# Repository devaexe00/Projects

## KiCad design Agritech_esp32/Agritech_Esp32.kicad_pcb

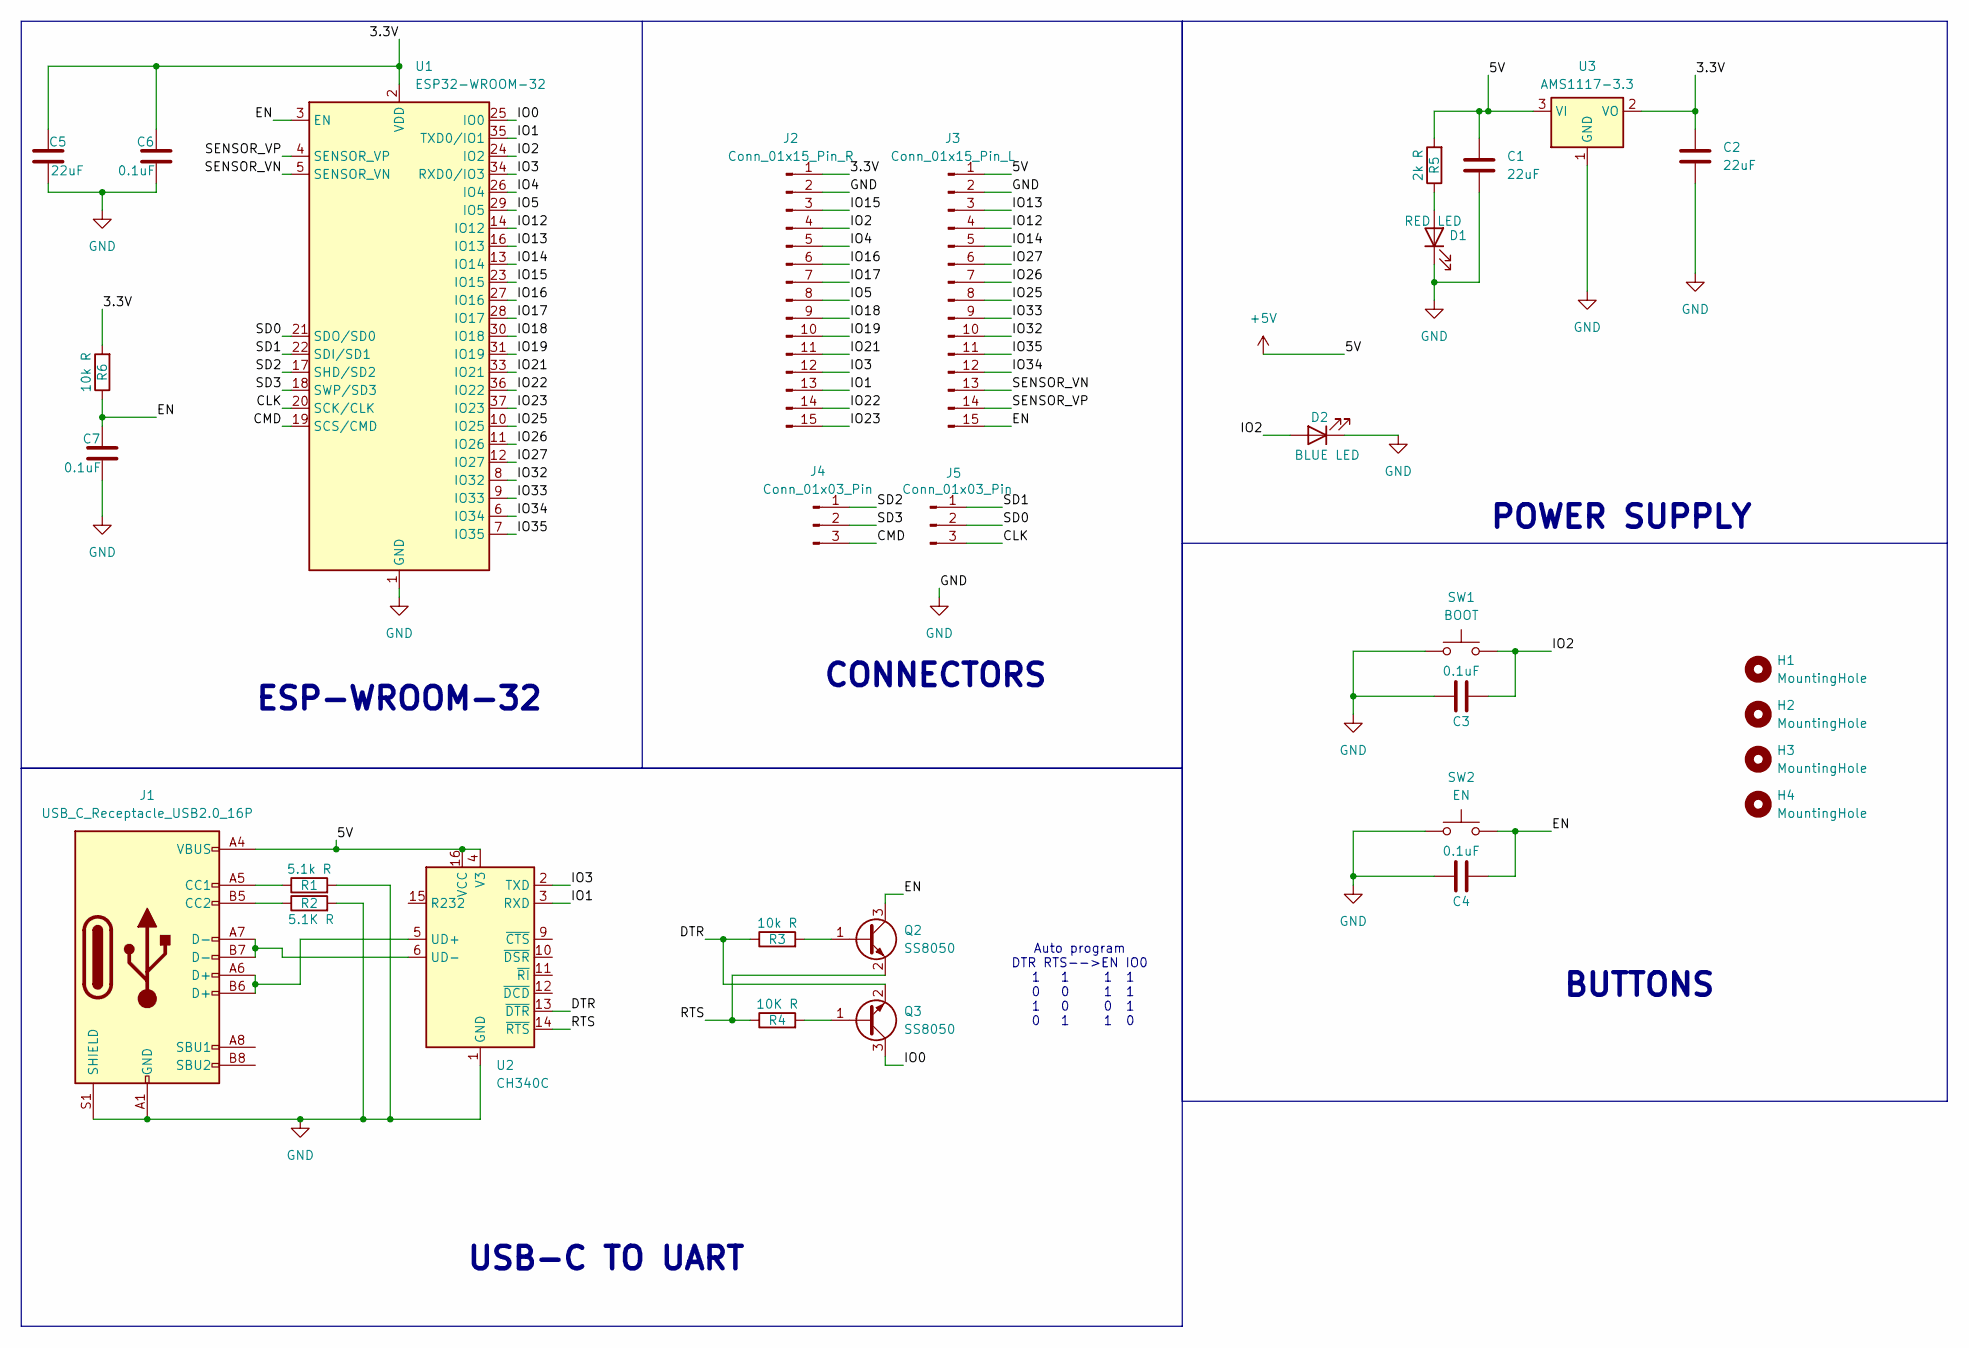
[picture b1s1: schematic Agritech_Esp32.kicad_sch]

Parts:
C1, C2, C5: 22uF; CP_Radial_D5.0mm_P2.50mm
C3, C4, C6, C7: 0.1uF; CP_Radial_D5.0mm_P2.50mm
D1: RED LED; LED_D5.0mm
D2: BLUE LED; LED_D5.0mm
H1, H2, H3, H4: MountingHole; MountingHole_2.5mm
J1: USB_C_Receptacle_USB2.0_16P; USB_C_Receptacle_HRO_TYPE-C-31-M-12
J2: Conn_01x15_Pin_R; PinHeader_1x15_P2.54mm_Vertical
J3: Conn_01x15_Pin_L; PinHeader_1x15_P2.54mm_Vertical
J4, J5: Conn_01x03_Pin; PinHeader_1x03_P2.54mm_Vertical
Q2, Q3: SS8050; SOT-23
R1: 5.1k R; R_Axial_DIN0309_L9.0mm_D3.2mm_P12.70mm_Horizontal
R2: 5.1K R; R_Axial_DIN0309_L9.0mm_D3.2mm_P12.70mm_Horizontal
R3, R6: 10k R; R_Axial_DIN0309_L9.0mm_D3.2mm_P12.70mm_Horizontal
R4: 10K R; R_Axial_DIN0309_L9.0mm_D3.2mm_P12.70mm_Horizontal
R5: 2k R; R_Axial_DIN0309_L9.0mm_D3.2mm_P12.70mm_Horizontal
SW1: BOOT; SW_Push_1P1T_NO_CK_KSC7xxJ
SW2: EN; SW_Push_1P1T_NO_CK_KSC7xxJ
U1: ESP32-WROOM-32
U2: CH340C; SOIC-16_3.9x9.9mm_P1.27mm
U3: AMS1117-3.3; SOT-223-3_TabPin2

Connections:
+5V: C1.1, J1.A4 (VBUS), J1.A9 (VBUS), J1.B4 (VBUS), J1.B9 (VBUS), J3.1, R5.2, U2.4 (V3), U2.16 (VCC), U3.3 (VI)
/3.3V: C2.1, C5.1, C6.2, J2.1, R6.2, U1.2 (VDD), U3.2 (VO)
/CLK: J5.3, U1.20 (SCK/CLK)
/CMD: J4.3, U1.19 (SCS/CMD)
/DTR: Q3.2 (E), R3.1, U2.13 (~DTR)
/EN: C4.2, C7.2, J3.15, Q2.3 (C), R6.1, SW2.2, U1.3 (EN)
/IO0: Q3.3 (C), U1.25 (IO0)
/IO1: J2.13, U1.35 (TXD0/IO1), U2.3 (RXD)
/IO2: C3.2, D2.2 (A), J2.4, SW1.2, U1.24 (IO2)
/IO3: J2.12, U1.34 (RXD0/IO3), U2.2 (TXD)
/IO4: J2.5, U1.26 (IO4)
/IO5: J2.8, U1.29 (IO5)
/IO12: J3.4, U1.14 (IO12)
/IO13: J3.3, U1.16 (IO13)
/IO14: J3.5, U1.13 (IO14)
/IO15: J2.3, U1.23 (IO15)
/IO16: J2.6, U1.27 (IO16)
/IO17: J2.7, U1.28 (IO17)
/IO18: J2.9, U1.30 (IO18)
/IO19: J2.10, U1.31 (IO19)
/IO21: J2.11, U1.33 (IO21)
/IO22: J2.14, U1.36 (IO22)
/IO23: J2.15, U1.37 (IO23)
/IO25: J3.8, U1.10 (IO25)
/IO26: J3.7, U1.11 (IO26)
/IO27: J3.6, U1.12 (IO27)
/IO32: J3.10, U1.8 (IO32)
/IO33: J3.9, U1.9 (IO33)
/IO34: J3.12, U1.6 (IO34)
/IO35: J3.11, U1.7 (IO35)
/RTS: Q2.2 (E), R4.1, U2.14 (~RTS)
/SD0: J5.2, U1.21 (SDO/SD0)
/SD1: J5.1, U1.22 (SDI/SD1)
/SD2: J4.1, U1.17 (SHD/SD2)
/SD3: J4.2, U1.18 (SWP/SD3)
/SENSOR_VN: J3.13, U1.5 (SENSOR_VN)
/SENSOR_VP: J3.14, U1.4 (SENSOR_VP)
GND: C1.2, C2.2, C3.1, C4.1, C5.2, C6.1, C7.1, D1.1 (K), D2.1 (K), J1.A1 (GND), J1.A12 (GND), J1.B1 (GND), J1.B12 (GND), J1.S1 (SHIELD), J2.2, J3.2, R1.2, R2.2, SW1.1, SW2.1, U1.1 (GND), U1.15 (GND), U1.38 (GND), U1.39 (GND), U2.1 (GND), U3.1 (GND)
unnamed: D1.2 (A), R5.1
unnamed: J1.A5 (CC1), R1.1
unnamed: J1.B5 (CC2), R2.1
unnamed: Q2.1 (B), R3.2
unnamed: Q3.1 (B), R4.2
unnamed: J1.A6 (D+), J1.B6 (D+), U2.5 (UD+)
unnamed: J1.A7 (D-), J1.B7 (D-), U2.6 (UD-)

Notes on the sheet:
USB-C TO UART
ESP-WROOM-32
POWER SUPPLY
Auto program DTR RTS-->EN IO0 1 1 1 1 0 0 1 1 1 0 0 1 0 1 1 0
CONNECTORS
BUTTONS

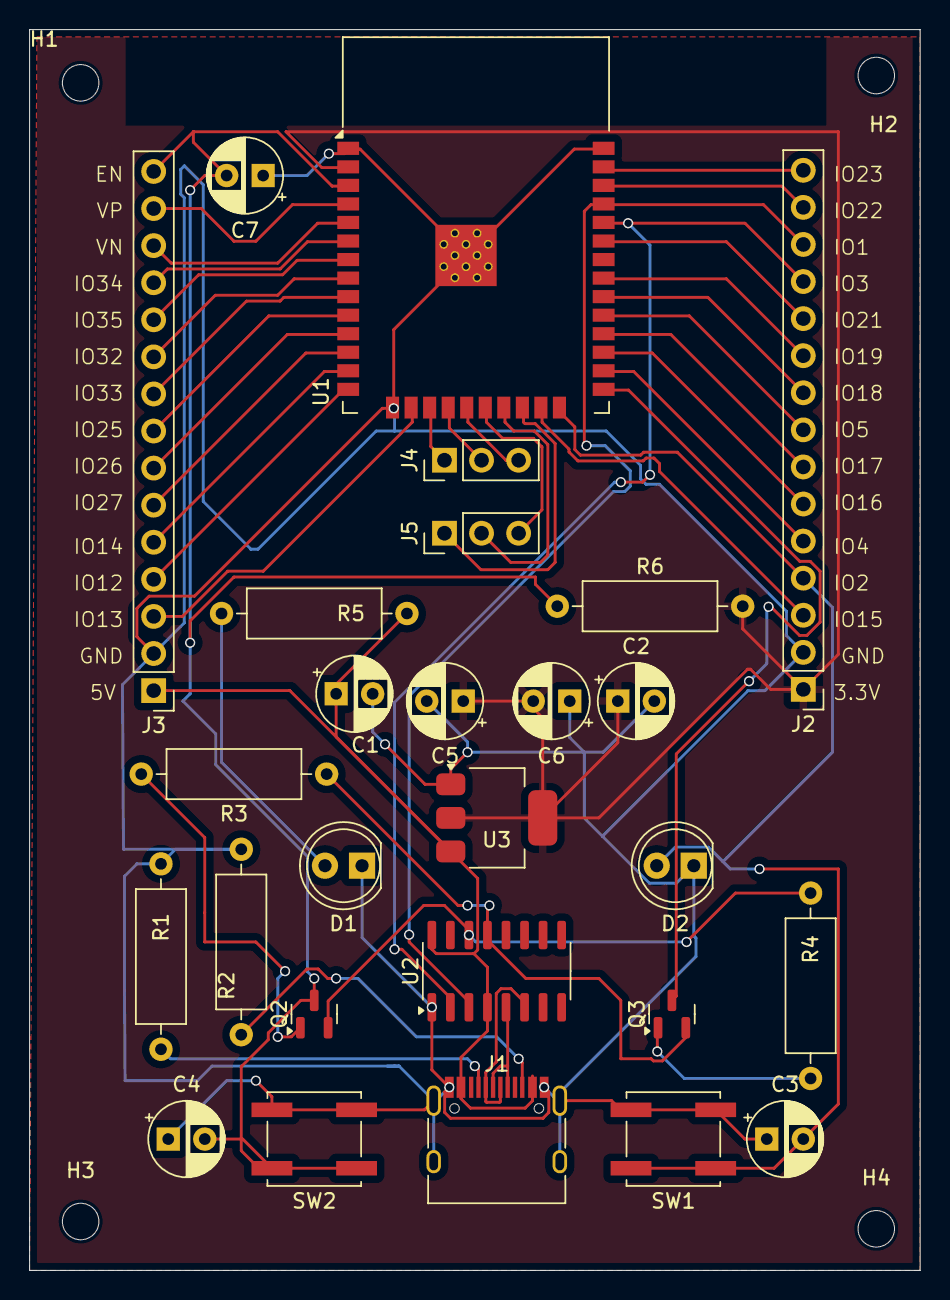
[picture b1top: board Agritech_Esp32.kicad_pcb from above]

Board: 2 copper layers, 61.0 x 85.0 mm, 31 parts (0 on the bottom side), 45 nets.

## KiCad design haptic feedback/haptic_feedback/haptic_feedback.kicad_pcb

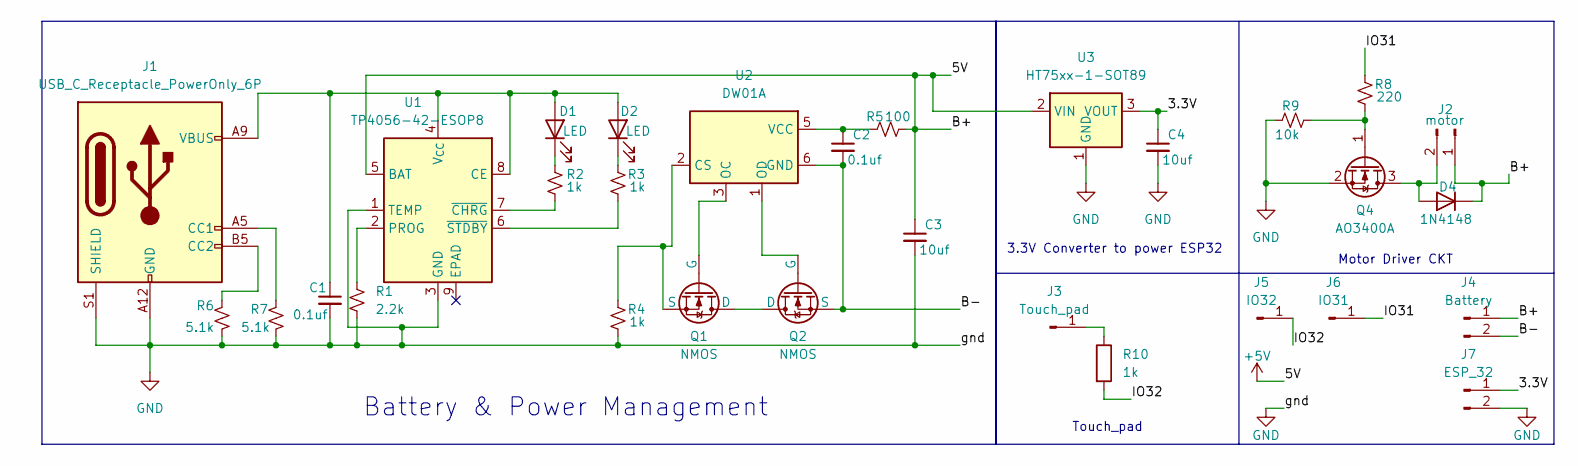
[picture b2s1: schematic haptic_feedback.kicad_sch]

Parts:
C1, C2: 0.1uf; C_0805_2012Metric
C3, C4: 10uf; C_0805_2012Metric
D1, D2: LED; LED_0805_2012Metric
D4: 1N4148; D_SOD-123
J1: USB_C_Receptacle_PowerOnly_6P; USB_C_Receptacle_GCT_USB4125-xx-x-0190_6P_TopMnt_Horizontal
J2: motor; JST_NV_B02P-NV_1x02_P5.00mm_Vertical
J3: Touch_pad; Touch_pad_10mm
J4: Battery; JST_NV_B02P-NV_1x02_P5.00mm_Vertical
J5: IO32; PinSocket_1x01_P2.54mm_Vertical
J6: IO31; PinSocket_1x01_P2.54mm_Vertical
J7: ESP_32; PinSocket_1x02_P2.54mm_Vertical
Q1, Q2: NMOS; SOT-23
Q4: AO3400A; SOT-23
R1: 2.2k; R_0805_2012Metric
R2, R3, R4, R10: 1k; R_0805_2012Metric
R5: 100; R_0805_2012Metric
R6, R7: 5.1k; R_0805_2012Metric
R8: 220; R_0805_2012Metric
R9: 10k; R_0805_2012Metric
U1: TP4056-42-ESOP8; SOIC-8-1EP_3.9x4.9mm_P1.27mm_EP2.41x3.3mm_ThermalVias
U2: DW01A; SOT-23-6
U3: HT75xx-1-SOT89; SOT-89-3

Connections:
+5V: C3.1, D4.1 (K), J2.1, J4.1, R5.2, U1.5 (BAT), U3.2 (VIN)
/3.3V: C4.1, J7.1, U3.3 (VOUT)
/B-: C2.2, J4.2, Q2.3 (S), U2.6 (GND)
/IO31: J6.1, R8.1
/IO32: J5.1, R10.2
GND: C1.2, C3.2, C4.2, J1.A12 (GND), J1.B12 (GND), J1.S1 (SHIELD), J7.2, Q4.2 (S), R1.2, R4.2, R6.2, R7.2, R9.1, U1.1 (TEMP), U1.3 (GND), U3.1 (GND)
unnamed: C1.1, D1.2 (A), D2.2 (A), J1.A9 (VBUS), J1.B9 (VBUS), U1.4 (V_{CC}), U1.8 (CE)
unnamed: D1.1 (K), R2.1
unnamed: D2.1 (K), R3.1
unnamed: D4.2 (A), J2.2, Q4.3 (D)
unnamed: J1.A5 (CC1), R7.1
unnamed: J1.B5 (CC2), R6.1
unnamed: J3.1, R10.1
unnamed: Q1.1 (D), Q2.1 (D)
unnamed: Q1.2 (G), U2.3 (OC)
unnamed: Q1.3 (S), R4.1, U2.2 (CS)
unnamed: Q2.2 (G), U2.1 (OD)
unnamed: Q4.1 (G), R8.2, R9.2
unnamed: R1.1, U1.2 (PROG)
unnamed: R2.2, U1.7 (~CHRG)
unnamed: R3.2, U1.6 (~STDBY)
unnamed: C2.1, R5.1, U2.5 (VCC)

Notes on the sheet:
Motor Driver CKT
3.3V Converter to power ESP32
Touch_pad
Battery & Power Management

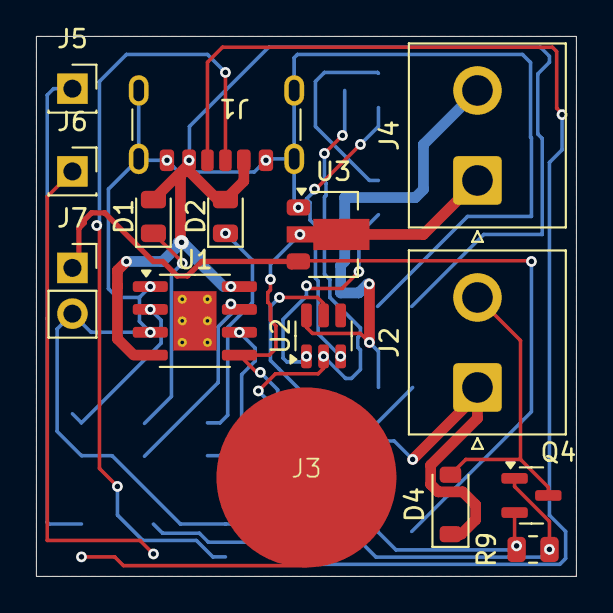
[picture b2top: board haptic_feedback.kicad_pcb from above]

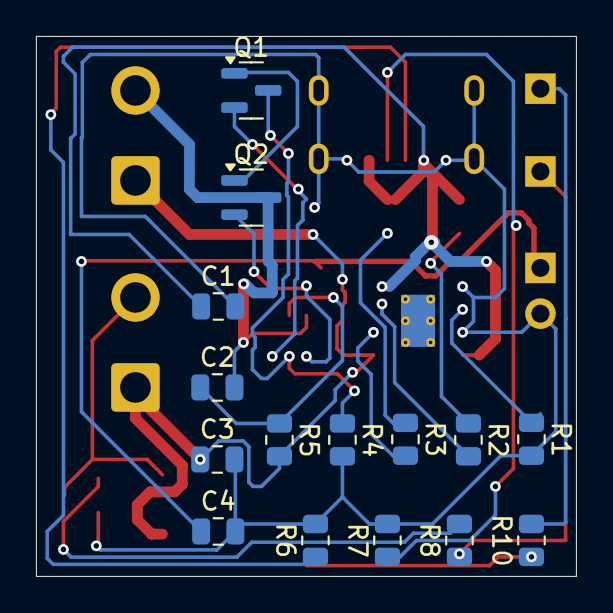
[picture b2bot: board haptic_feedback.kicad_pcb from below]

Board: 2 copper layers, 30.0 x 30.0 mm, 30 parts (15 on the bottom side), 22 nets.

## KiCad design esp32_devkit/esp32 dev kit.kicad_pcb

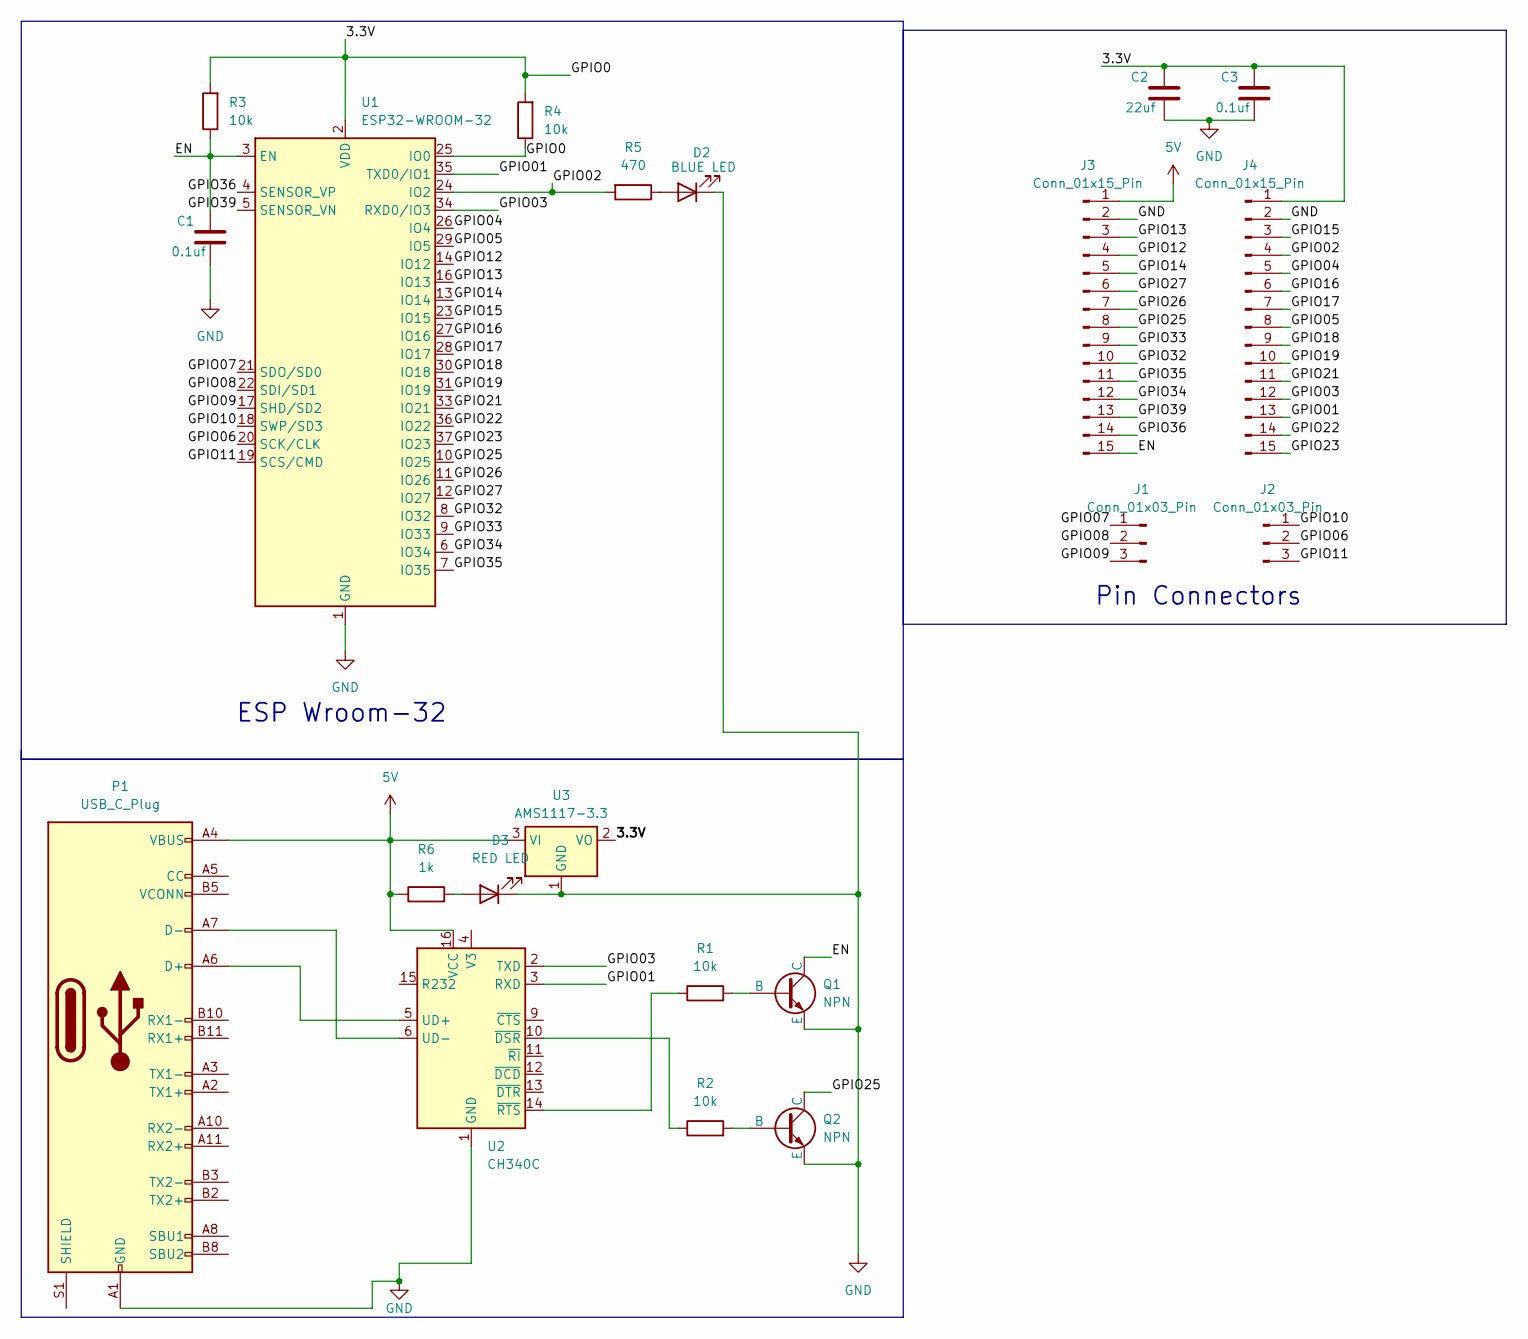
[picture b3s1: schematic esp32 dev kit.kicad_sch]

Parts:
C1, C3: 0.1uf; CP_Radial_D5.0mm_P2.50mm
C2: 22uf; CP_Radial_D5.0mm_P2.50mm
D2: BLUE LED; LED_D5.0mm
D3: RED LED; LED_D5.0mm
J1, J2: Conn_01x03_Pin; PinHeader_1x03_P2.54mm_Vertical
J3, J4: Conn_01x15_Pin; PinHeader_1x15_P2.54mm_Vertical
P1: USB_C_Plug; USB_C_Receptacle_HCTL_HC-TYPE-C-16P-01A
Q1, Q2: NPN; TO-92
R1, R2, R3, R4: 10k; R_Axial_DIN0207_L6.3mm_D2.5mm_P7.62mm_Horizontal
R5: 470; R_Axial_DIN0207_L6.3mm_D2.5mm_P7.62mm_Horizontal
R6: 1k; R_Axial_DIN0207_L6.3mm_D2.5mm_P7.62mm_Horizontal
U1: ESP32-WROOM-32
U2: CH340C; SOIC-16_3.9x9.9mm_P1.27mm
U3: AMS1117-3.3; SOT-223-3_TabPin2

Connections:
5V: J3.1, P1.A4 (VBUS), P1.A9 (VBUS), P1.B4 (VBUS), P1.B9 (VBUS), R6.1, U2.16 (VCC), U3.3 (VI)
/3.3V: C2.1, C3.1, J4.1, R3.2, R4.1, R4.2, U1.2 (VDD), U1.25 (IO0), U3.2 (VO)
/EN: C1.1, J3.15, Q1.1 (C), R3.1, U1.3 (EN)
/GPIO01: J4.13, U1.35 (TXD0/IO1), U2.3 (RXD)
/GPIO02: J4.4, R5.2, U1.24 (IO2)
/GPIO03: J4.12, U1.34 (RXD0/IO3), U2.2 (TXD)
/GPIO04: J4.5, U1.26 (IO4)
/GPIO05: J4.8, U1.29 (IO5)
/GPIO06: J2.2, U1.20 (SCK/CLK)
/GPIO07: J1.1, U1.21 (SDO/SD0)
/GPIO08: J1.2, U1.22 (SDI/SD1)
/GPIO09: J1.3, U1.17 (SHD/SD2)
/GPIO10: J2.1, U1.18 (SWP/SD3)
/GPIO11: J2.3, U1.19 (SCS/CMD)
/GPIO12: J3.4, U1.14 (IO12)
/GPIO13: J3.3, U1.16 (IO13)
/GPIO14: J3.5, U1.13 (IO14)
/GPIO15: J4.3, U1.23 (IO15)
/GPIO16: J4.6, U1.27 (IO16)
/GPIO17: J4.7, U1.28 (IO17)
/GPIO18: J4.9, U1.30 (IO18)
/GPIO19: J4.10, U1.31 (IO19)
/GPIO21: J4.11, U1.33 (IO21)
/GPIO22: J4.14, U1.36 (IO22)
/GPIO23: J4.15, U1.37 (IO23)
/GPIO25: J3.8, Q2.1 (C), U1.10 (IO25)
/GPIO26: J3.7, U1.11 (IO26)
/GPIO27: J3.6, U1.12 (IO27)
/GPIO32: J3.10, U1.8 (IO32)
/GPIO33: J3.9, U1.9 (IO33)
/GPIO34: J3.12, U1.6 (IO34)
/GPIO35: J3.11, U1.7 (IO35)
/GPIO36: J3.14, U1.4 (SENSOR_VP)
/GPIO39: J3.13, U1.5 (SENSOR_VN)
GND: C1.2, C2.2, C3.2, D2.1 (K), D3.1 (K), J3.2, J4.2, P1.A1 (GND), P1.A12 (GND), P1.B1 (GND), P1.B12 (GND), Q1.3 (E), Q2.3 (E), U1.1 (GND), U1.15 (GND), U1.38 (GND), U1.39 (GND), U2.1 (GND), U3.1 (GND)
unnamed: D2.2 (A), R5.1
unnamed: D3.2 (A), R6.2
unnamed: P1.A6 (D+), U2.5 (UD+)
unnamed: P1.A7 (D-), U2.6 (UD-)
unnamed: Q1.2 (B), R1.2
unnamed: Q2.2 (B), R2.2
unnamed: R2.1, U2.10 (~DSR)
unnamed: R1.1, U2.14 (~RTS)

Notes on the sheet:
ESP Wroom-32
Pin Connectors

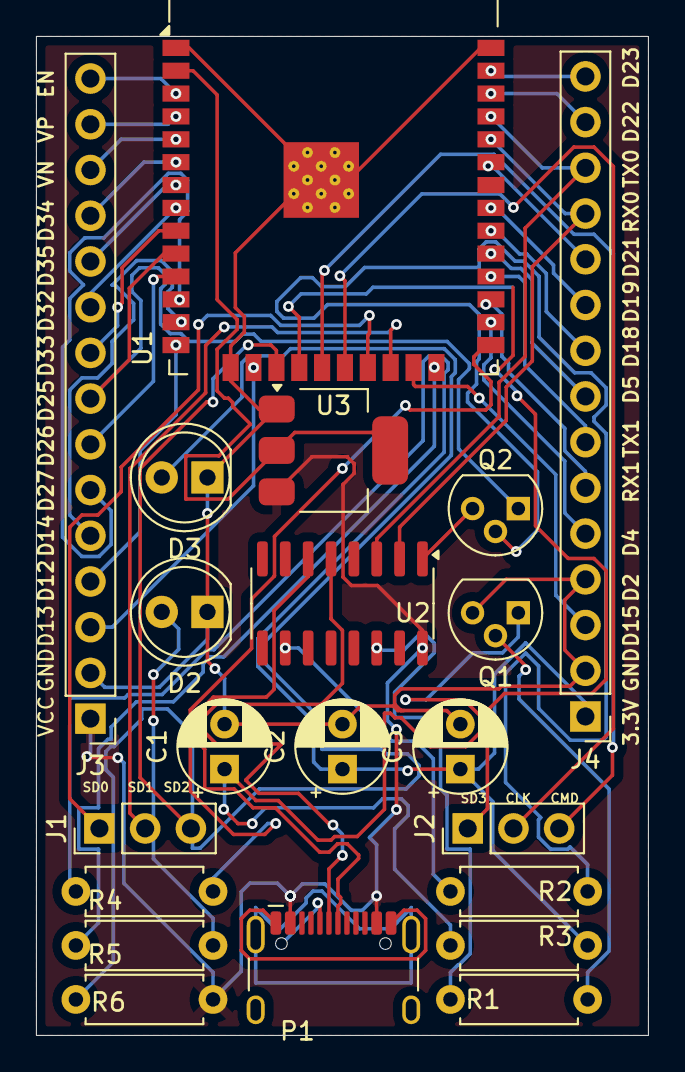
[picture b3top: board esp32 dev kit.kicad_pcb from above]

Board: 2 copper layers, 34.0 x 55.5 mm, 21 parts (0 on the bottom side), 43 nets.

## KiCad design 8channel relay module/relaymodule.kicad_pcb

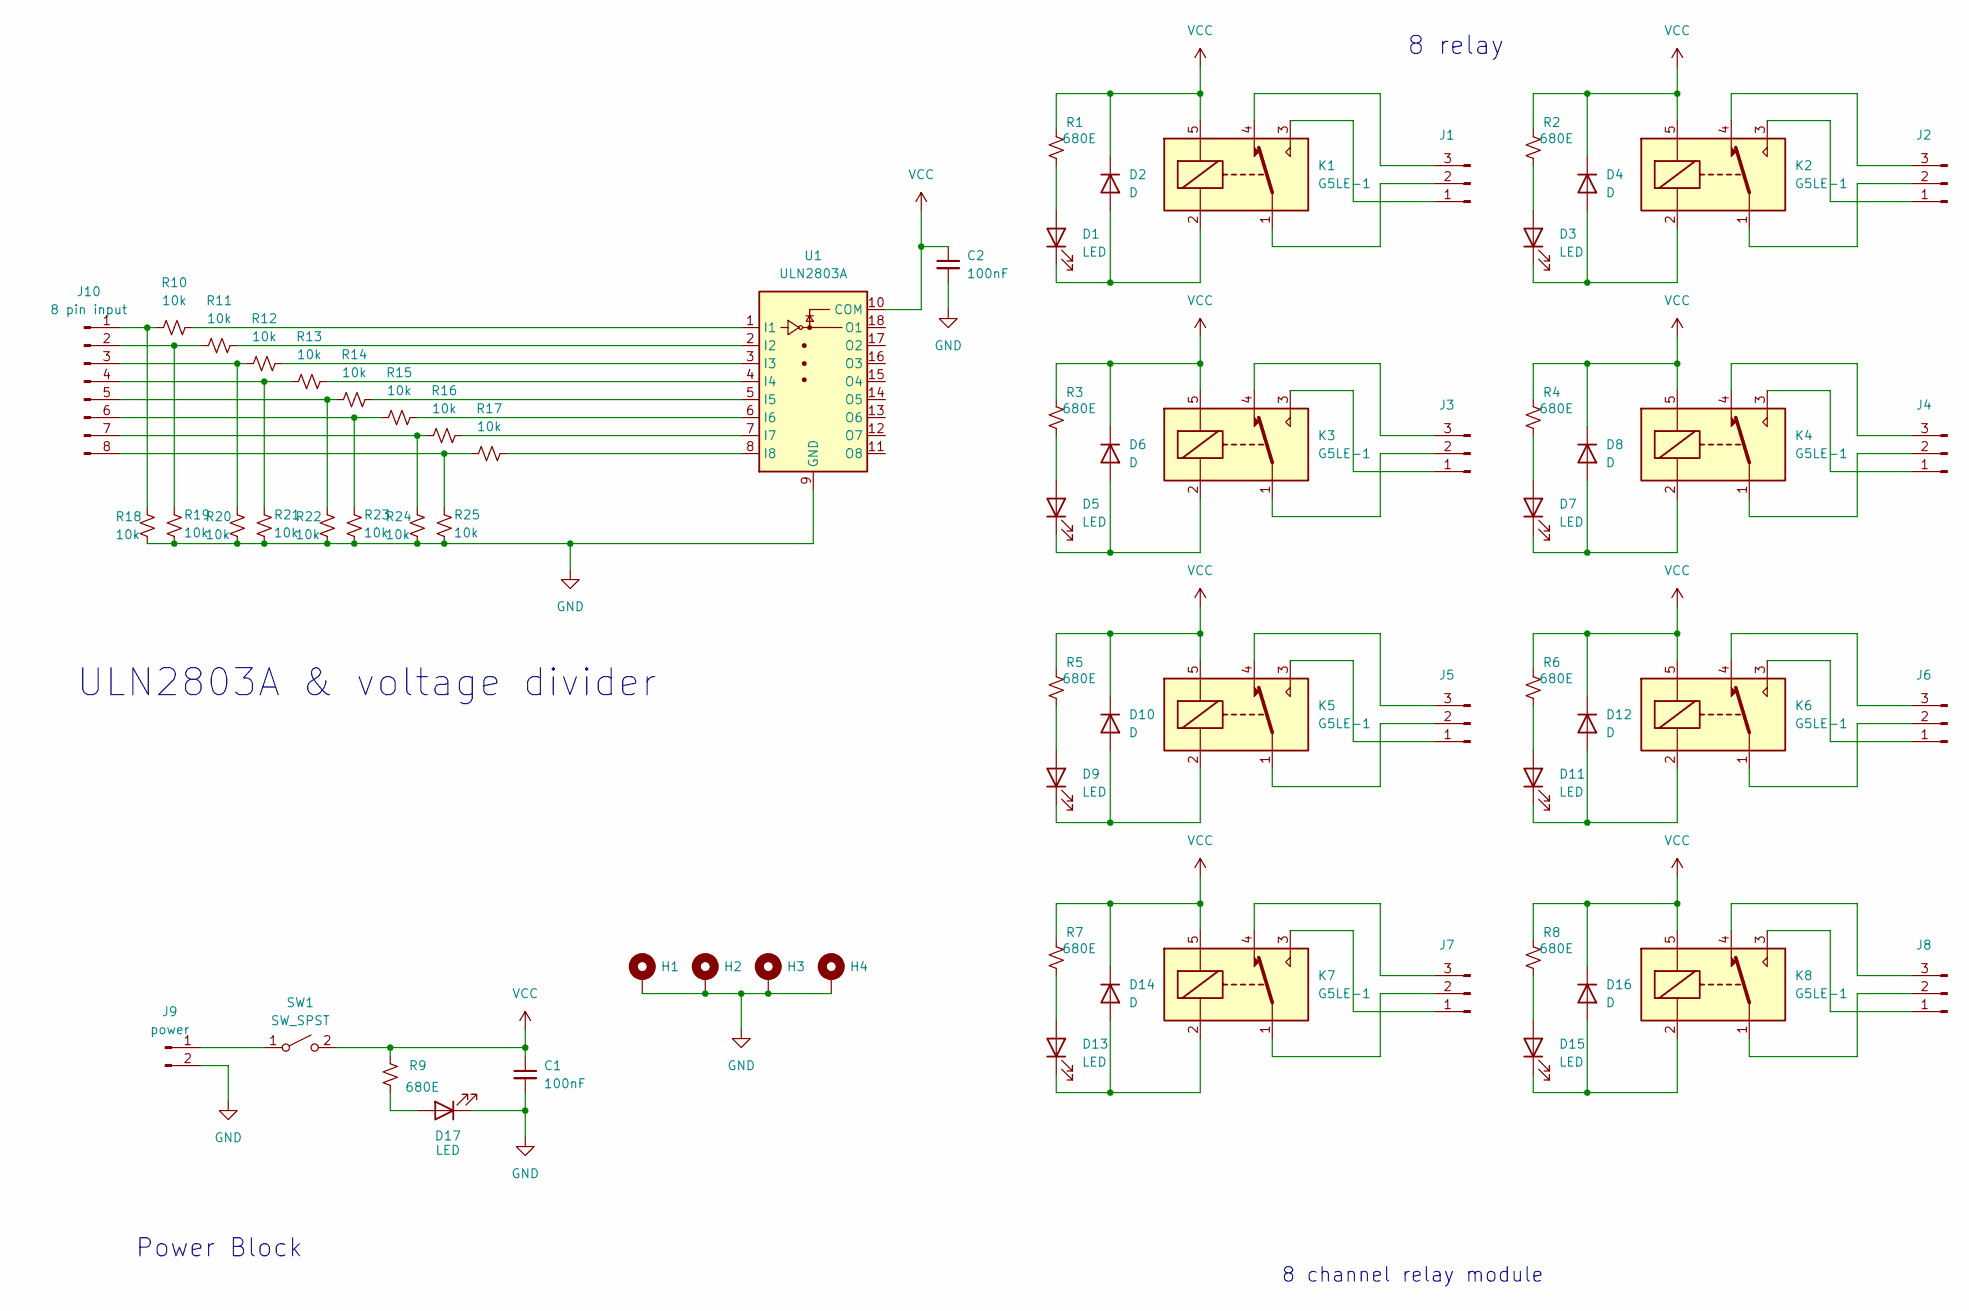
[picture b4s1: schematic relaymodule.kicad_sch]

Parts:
C1, C2: 100nF; C_0805_2012Metric_Pad1.18x1.45mm_HandSolder
D1, D3, D5, D7, D9, D11, D13, D15, D17: LED; LED_1206_3216Metric
D2, D4, D6, D8, D10, D12, D14, D16: D; D_1206_3216Metric
H1, H2, H3, H4: MountingHole_2.5mm_Pad_Via
J1, J2, J3, J4, J5, J6, J7, J8: JST_NV_B03P-NV_1x03_P5.00mm_Vertical
J9: power; JST_NV_B02P-NV_1x02_P5.00mm_Vertical
J10: 8 pin input; PinHeader_1x08_P2.54mm_Vertical
K1, K2, K3, K4, K5, K6, K7, K8: G5LE-1; Relay_SPDT_Omron-G5LE-1
R1, R2, R3, R4, R5, R6, R7, R8, R9: 680E; R_0805_2012Metric_Pad1.20x1.40mm_HandSolder
R10, R11, R12, R13, R14, R15, R16, R17, R18, R19, R20, R21, R22, R23, R24, R25: 10k; R_0805_2012Metric_Pad1.20x1.40mm_HandSolder
SW1: SW_SPST; Panasonic_EVQPUJ_EVQPUA
U1: ULN2803A; DIP-18_W7.62mm

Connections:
GND: C1.2, C2.2, D17.1 (K), H1.1, H2.1, H3.1, H4.1, J9.2, R18.2, R19.2, R20.2, R21.2, R22.2, R23.2, R24.2, R25.2, U1.9 (GND)
unnamed: D1.2 (A), R1.2
unnamed: D1.1 (K), D2.2 (A), K1.2
unnamed: D3.2 (A), R2.2
unnamed: D3.1 (K), D4.2 (A), K2.2
unnamed: D5.2 (A), R3.2
unnamed: D5.1 (K), D6.2 (A), K3.2
unnamed: D7.2 (A), R4.2
unnamed: D7.1 (K), D8.2 (A), K4.2
unnamed: D9.2 (A), R5.2
unnamed: D9.1 (K), D10.2 (A), K5.2
unnamed: D11.2 (A), R6.2
unnamed: D11.1 (K), D12.2 (A), K6.2
unnamed: D13.2 (A), R7.2
unnamed: D13.1 (K), D14.2 (A), K7.2
unnamed: D15.2 (A), R8.2
unnamed: D15.1 (K), D16.2 (A), K8.2
unnamed: D17.2 (A), R9.2
unnamed: J1.1, K1.3
unnamed: J1.2, K1.1
unnamed: J1.3, K1.4
unnamed: J2.1, K2.3
unnamed: J2.2, K2.1
unnamed: J2.3, K2.4
unnamed: J3.1, K3.3
unnamed: J3.2, K3.1
unnamed: J3.3, K3.4
unnamed: J4.1, K4.3
unnamed: J4.2, K4.1
unnamed: J4.3, K4.4
unnamed: J5.1, K5.3
unnamed: J5.2, K5.1
unnamed: J5.3, K5.4
unnamed: J6.1, K6.3
unnamed: J6.2, K6.1
unnamed: J6.3, K6.4
unnamed: J7.1, K7.3
unnamed: J7.2, K7.1
unnamed: J7.3, K7.4
unnamed: J8.1, K8.3
unnamed: J8.2, K8.1
unnamed: J8.3, K8.4
unnamed: J9.1, SW1.1 (A)
unnamed: J10.1, R10.1, R18.1
unnamed: J10.2, R11.1, R19.1
unnamed: J10.3, R12.1, R20.1
unnamed: J10.4, R13.1, R21.1
unnamed: J10.5, R14.1, R22.1
unnamed: J10.6, R15.1, R23.1
unnamed: J10.7, R16.1, R24.1
unnamed: J10.8, R17.1, R25.1
unnamed: R10.2, U1.1 (I1)
unnamed: R11.2, U1.2 (I2)
unnamed: R12.2, U1.3 (I3)
unnamed: R13.2, U1.4 (I4)
unnamed: R14.2, U1.5 (I5)
unnamed: R15.2, U1.6 (I6)
unnamed: R16.2, U1.7 (I7)
unnamed: R17.2, U1.8 (I8)
VCC: C1.1, C2.1, D2.1 (K), D4.1 (K), D6.1 (K), D8.1 (K), D10.1 (K), D12.1 (K), D14.1 (K), D16.1 (K), K1.5, K2.5, K3.5, K4.5, K5.5, K6.5, K7.5, K8.5, R1.1, R2.1, R3.1, R4.1, R5.1, R6.1, R7.1, R8.1, R9.1, SW1.2 (B), U1.10 (COM)

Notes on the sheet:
Power Block
8 channel relay module
8 relay
ULN2803A & voltage divider

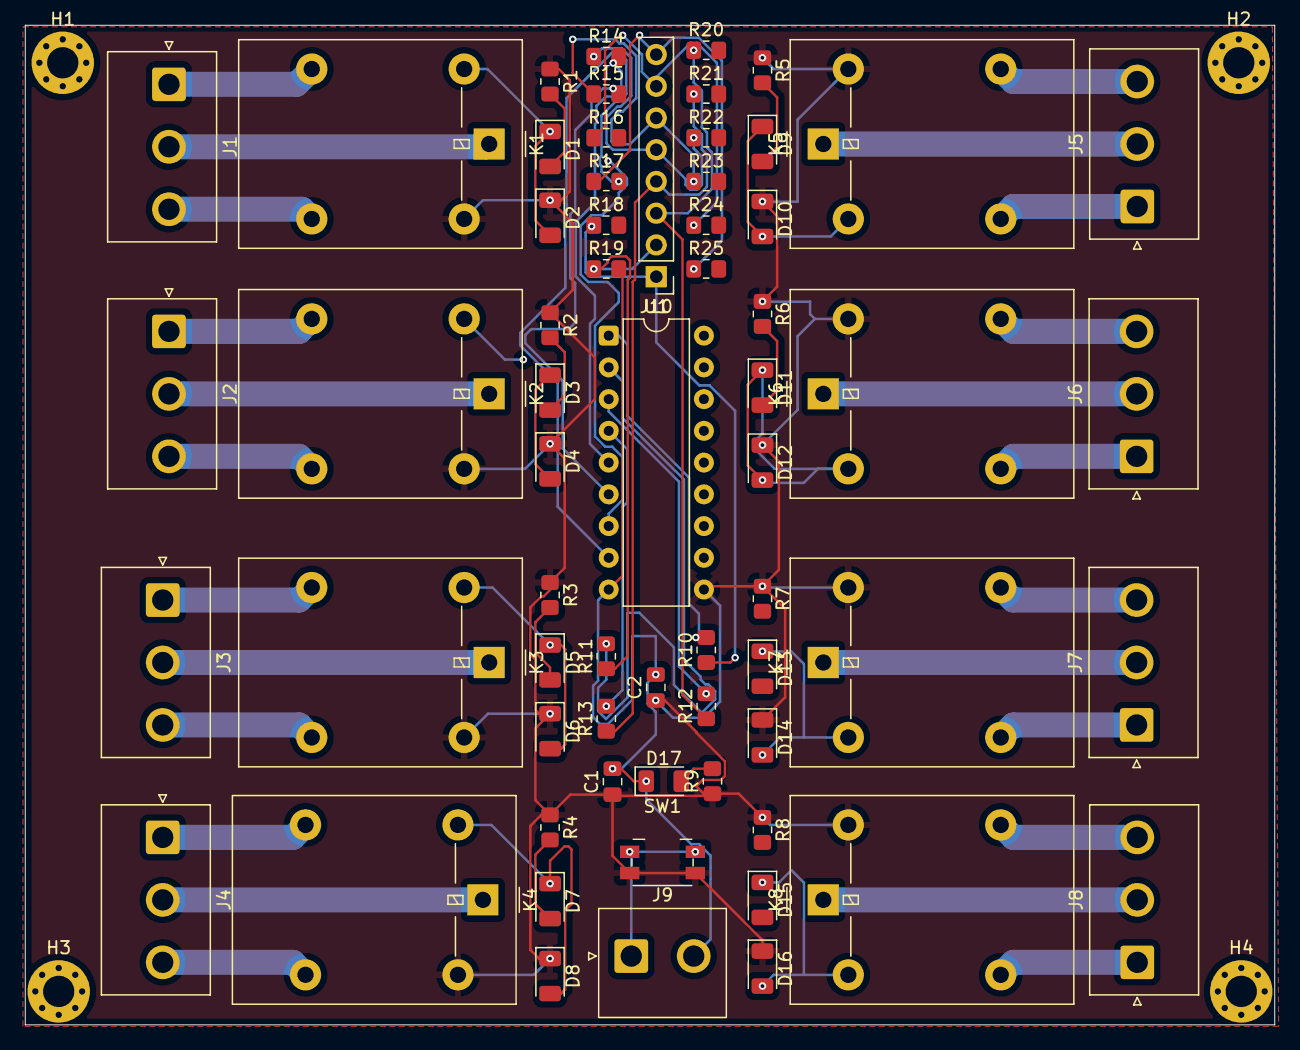
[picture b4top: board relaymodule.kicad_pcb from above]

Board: 2 copper layers, 100.0 x 80.0 mm, 68 parts (0 on the bottom side), 60 nets.

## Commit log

2026-01-11 added smarthome
2026-02-08 added[haptic feedback] folder
2026-02-20 Agritech_esp32
